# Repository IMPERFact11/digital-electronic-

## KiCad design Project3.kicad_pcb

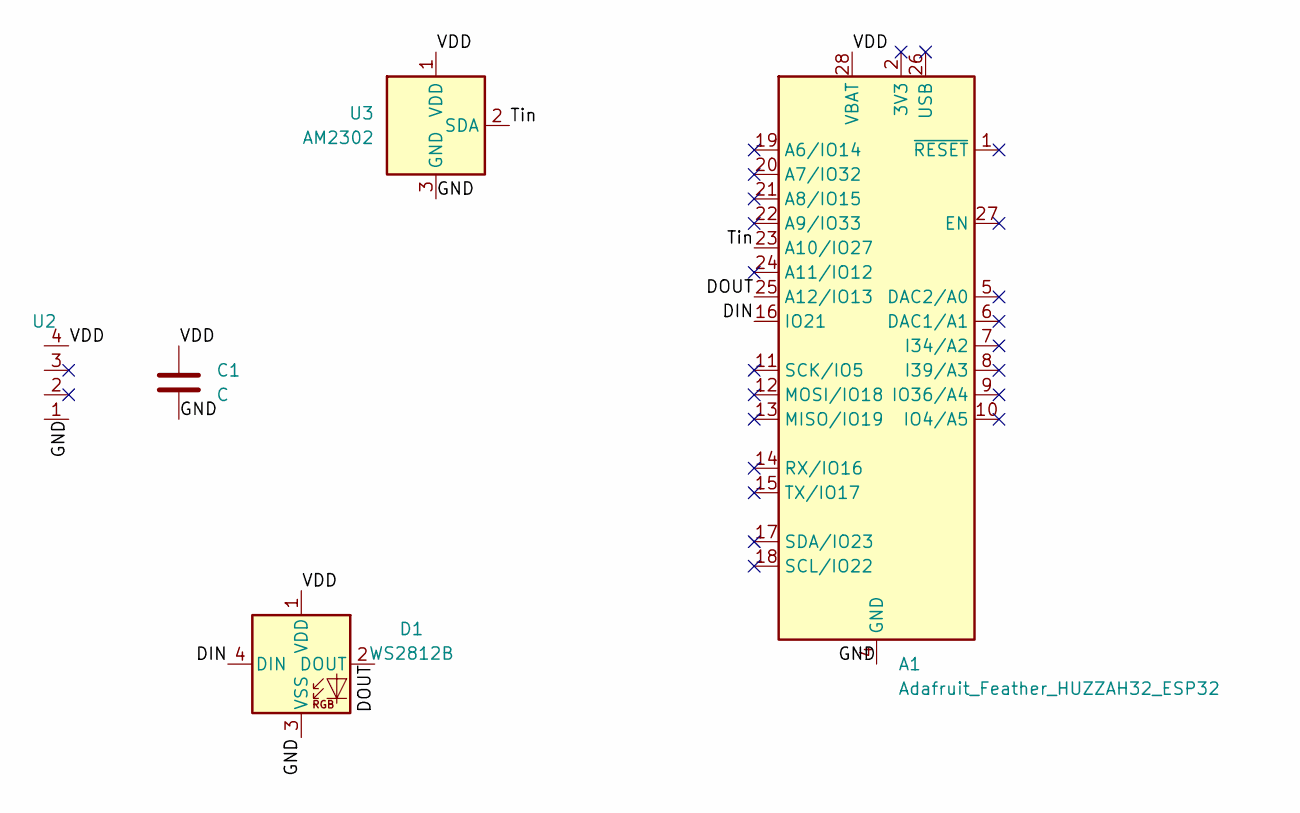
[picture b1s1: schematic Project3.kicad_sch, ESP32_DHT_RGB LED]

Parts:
A1: Adafruit_Feather_HUZZAH32_ESP32; Adafruit_Feather
C1: C; C_0805_2012Metric
D1: WS2812B; LED_WS2812B_PLCC4_5.0x5.0mm_P3.2mm
U2: PinHeader_1x04_P1.00mm_Vertical
U3: AM2302; ASAIR_AM2302_P2.54mm_Vertical

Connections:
/DIN: A1.16 (IO21), D1.4 (DIN)
/DOUT: A1.25 (A12/IO13), D1.2 (DOUT)
/GND: A1.4 (GND), C1.2, D1.3 (VSS), U2.1, U3.3 (GND), U3.4 (GND)
/Tin: A1.23 (A10/IO27), U3.2 (SDA)
/VDD: A1.28 (VBAT), C1.1, D1.1 (VDD), U2.4, U3.1 (VDD)

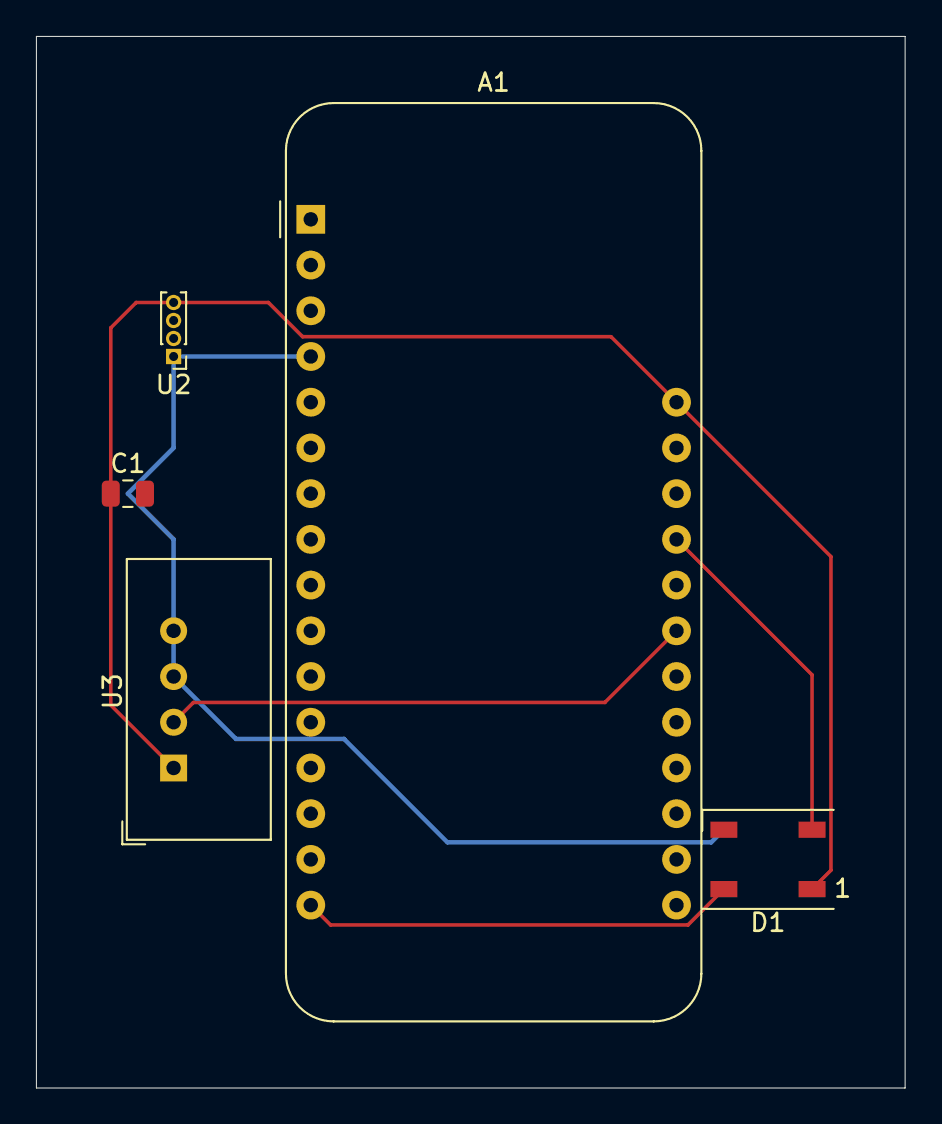
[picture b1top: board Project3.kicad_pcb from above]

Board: 2 copper layers, 48.3 x 58.4 mm, 5 parts (0 on the bottom side), 5 nets.
